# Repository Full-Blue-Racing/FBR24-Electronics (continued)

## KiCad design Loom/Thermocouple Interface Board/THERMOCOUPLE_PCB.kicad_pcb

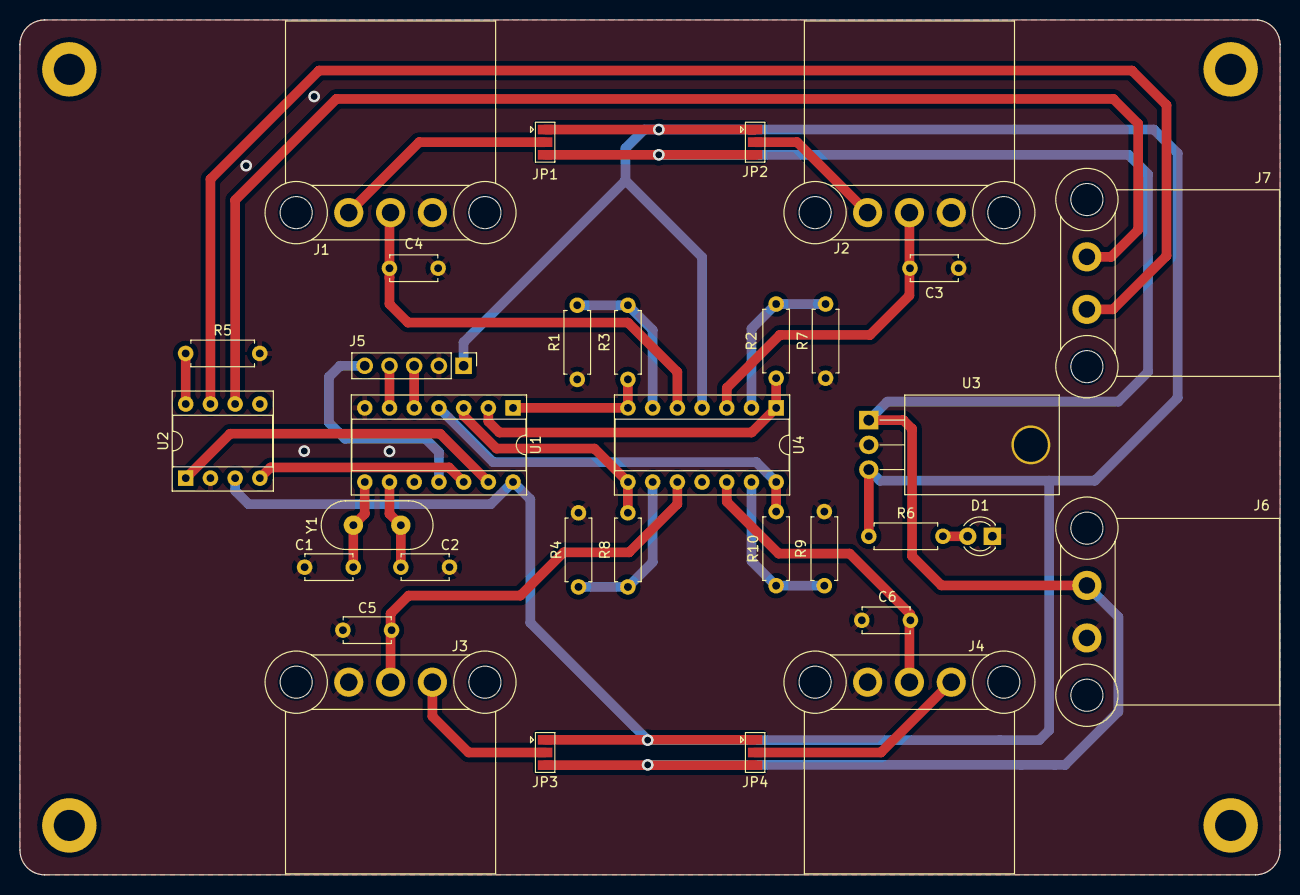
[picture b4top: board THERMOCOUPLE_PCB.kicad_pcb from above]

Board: 2 copper layers, 129.5 x 87.9 mm, 33 parts (0 on the bottom side), 30 nets.

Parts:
C1, C2: 27pF; C_Disc_D4.7mm_W2.5mm_P5.00mm
C3, C4, C5, C6: TBD; C_Disc_D4.7mm_W2.5mm_P5.00mm
D1: PWR LED; LED_D3.0mm
J1, J2, J3, J4: Conn_01x03; ATF13-3P-BM03
J5: Conn_01x05_Pin; PinHeader_1x05_P2.54mm_Vertical
J6, J7: Conn_01x02; ATF13-2P-BM03
JP1, JP2, JP3, JP4: SolderJumper_3_Open; SolderJumper-3_P1.3mm_Open_Pad1.0x1.5mm
R1, R2, R3, R4, R6, R7, R8, R9, R10: 220R; R_Axial_DIN0207_L6.3mm_D2.5mm_P7.62mm_Horizontal
R5: 20K; R_Axial_DIN0207_L6.3mm_D2.5mm_P7.62mm_Horizontal
U1: DIP-14_W7.62mm_Socket
U2: MCP2551-I-P; DIP-8_W7.62mm_Socket
U3: TL780-05KCS; TO-220-3_Horizontal_TabDown
U4: MCP6004; DIP-14_W7.62mm_Socket
Y1: Crystal; 9B-16.000MAAJ-B

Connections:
+5V: J5.1, JP1.1 (A), JP2.1 (A), JP3.1 (A), JP4.1 (A), R6.1, U1.14 (VDD), U2.3 (VDD), U3.3 (VO), U4.4 (V+)
+12V: J6.2, JP1.3 (B), JP2.3 (B), JP3.3 (B), JP4.3 (B), U3.1 (VI)
/AN0: R3.2, U1.1 (GP0), U4.7
/AN1: R2.2, U1.2 (GP1), U4.1
/AN2: R8.2, U1.3 (GP2), U4.8
/AN3: R10.2, U1.4 (GP3), U4.14
/CLK: J5.4, U1.6 (GP5)
/DATA: J5.3, U1.5 (GP4)
/PWR LED: D1.2 (A), R6.2
/RXCAN: U1.12 (RXCAN), U2.4 (RXD)
/TXCAN: U1.13 (TXCAN), U2.1 (TXD)
/VPP: J5.5, U1.11 (GP7)
GND: C1.2, C2.2, C3.2, C4.2, C5.2, C6.2, D1.1 (K), J1.1, J2.1, J3.1, J4.1, J5.2, J6.1, R1.1, R4.1, R5.2, R7.1, R9.1, U1.7 (VSS), U2.2 (VSS), U3.2 (GND)
unnamed: C4.1, J1.2, U4.5 (+)
unnamed: J1.3, JP1.2 (C)
unnamed: C3.1, J2.2, U4.3 (+)
unnamed: J2.3, JP2.2 (C)
unnamed: C5.1, J3.2, U4.10 (+)
unnamed: J3.3, JP3.2 (C)
unnamed: C6.1, J4.2, U4.12 (+)
unnamed: J4.3, JP4.2 (C)
unnamed: J7.1, U2.7 (CANH)
unnamed: J7.2, U2.6 (CANL)
unnamed: C1.1, U1.8 (OSC1), Y1.1
unnamed: C2.1, U1.9 (OSC2), Y1.2
unnamed: R5.1, U2.8 (Rs)
unnamed: R2.1, R7.2, U4.2 (-)
unnamed: R1.2, R3.1, U4.6 (-)
unnamed: R4.2, R8.1, U4.9 (-)
unnamed: R9.2, R10.1, U4.13 (-)

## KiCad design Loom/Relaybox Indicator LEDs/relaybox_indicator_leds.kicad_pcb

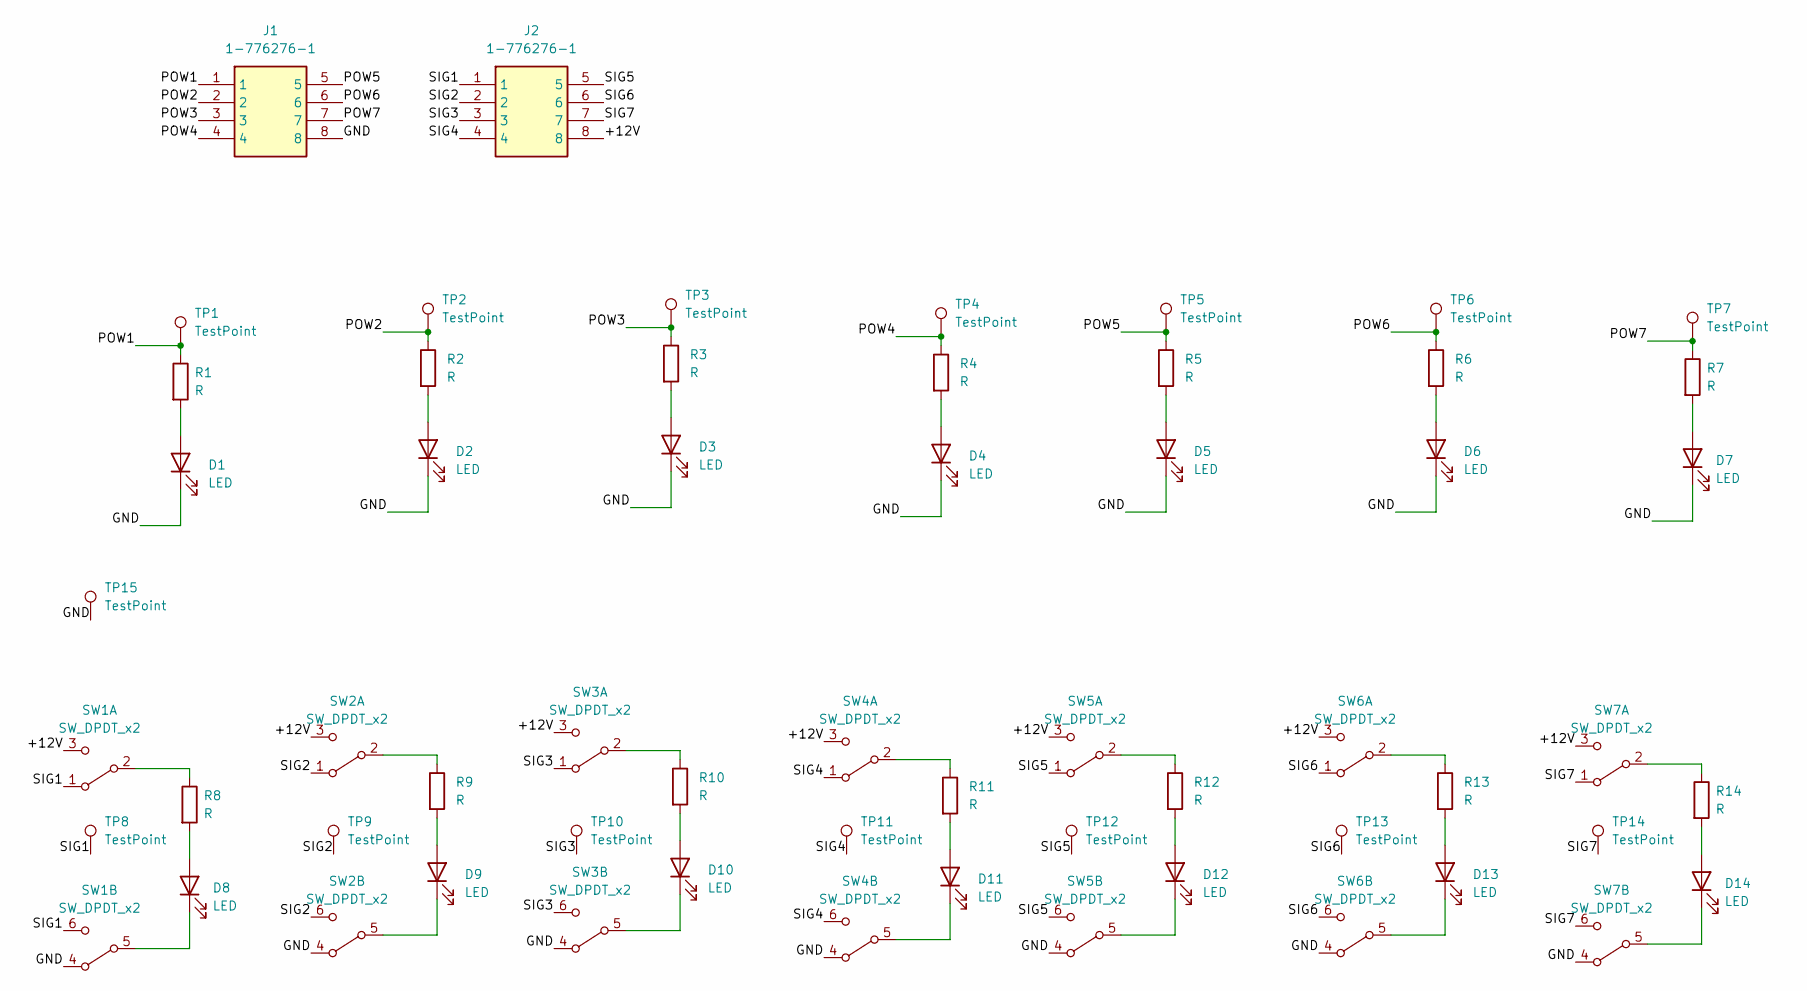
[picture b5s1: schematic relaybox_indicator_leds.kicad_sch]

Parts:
D1, D2, D3, D4, D5, D6, D7, D8, D9, D10, D11, D12, D13, D14: LED; LED_D5.0mm
J1, J2: 1-776276-1; 17762761; Mouser Part Number 571-1-776276-1
R1, R2, R3, R4, R5, R6, R7, R8, R9, R10, R11, R12, R13, R14: R; R_Axial_DIN0207_L6.3mm_D2.5mm_P10.16mm_Horizontal
SW1, SW2, SW3, SW4, SW5, SW6, SW7: SW_DPDT_x2; MP004696
TP1, TP2, TP3, TP4, TP5, TP6, TP7, TP8, TP9, TP10, TP11, TP12, TP13, TP14, TP15: TestPoint; TestPoint_THTPad_D3.0mm_Drill1.5mm

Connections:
/+12V: J2.8, SW1.3 (C), SW2.3 (C), SW3.3 (C), SW4.3 (C), SW5.3 (C), SW6.3 (C), SW7.3 (C)
/GND: D1.1 (K), D2.1 (K), D3.1 (K), D4.1 (K), D5.1 (K), D6.1 (K), D7.1 (K), J1.8, SW1.4 (A), SW2.4 (A), SW3.4 (A), SW4.4 (A), SW5.4 (A), SW6.4 (A), SW7.4 (A), TP15.1
/POW1: J1.1, R1.1, TP1.1
/POW2: J1.2, R2.1, TP2.1
/POW3: J1.3, R3.1, TP3.1
/POW4: J1.4, R4.1, TP4.1
/POW5: J1.5, R5.1, TP5.1
/POW6: J1.6, R6.1, TP6.1
/POW7: J1.7, R7.1, TP7.1
/SIG1: J2.1, SW1.1 (A), SW1.6 (C), TP8.1
/SIG2: J2.2, SW2.1 (A), SW2.6 (C), TP9.1
/SIG3: J2.3, SW3.1 (A), SW3.6 (C), TP10.1
/SIG4: J2.4, SW4.1 (A), SW4.6 (C), TP11.1
/SIG5: J2.5, SW5.1 (A), SW5.6 (C), TP12.1
/SIG6: J2.6, SW6.1 (A), SW6.6 (C), TP13.1
/SIG7: J2.7, SW7.1 (A), SW7.6 (C), TP14.1
unnamed: D1.2 (A), R1.2
unnamed: D2.2 (A), R2.2
unnamed: D3.2 (A), R3.2
unnamed: D4.2 (A), R4.2
unnamed: D5.2 (A), R5.2
unnamed: D6.2 (A), R6.2
unnamed: D7.2 (A), R7.2
unnamed: D8.2 (A), R8.2
unnamed: D8.1 (K), SW1.5 (B)
unnamed: D9.2 (A), R9.2
unnamed: D9.1 (K), SW2.5 (B)
unnamed: D10.2 (A), R10.2
unnamed: D10.1 (K), SW3.5 (B)
unnamed: D11.2 (A), R11.2
unnamed: D11.1 (K), SW4.5 (B)
unnamed: D12.2 (A), R12.2
unnamed: D12.1 (K), SW5.5 (B)
unnamed: D13.2 (A), R13.2
unnamed: D13.1 (K), SW6.5 (B)
unnamed: D14.2 (A), R14.2
unnamed: D14.1 (K), SW7.5 (B)
unnamed: R8.1, SW1.2 (B)
unnamed: R9.1, SW2.2 (B)
unnamed: R10.1, SW3.2 (B)
unnamed: R11.1, SW4.2 (B)
unnamed: R12.1, SW5.2 (B)
unnamed: R13.1, SW6.2 (B)
unnamed: R14.1, SW7.2 (B)

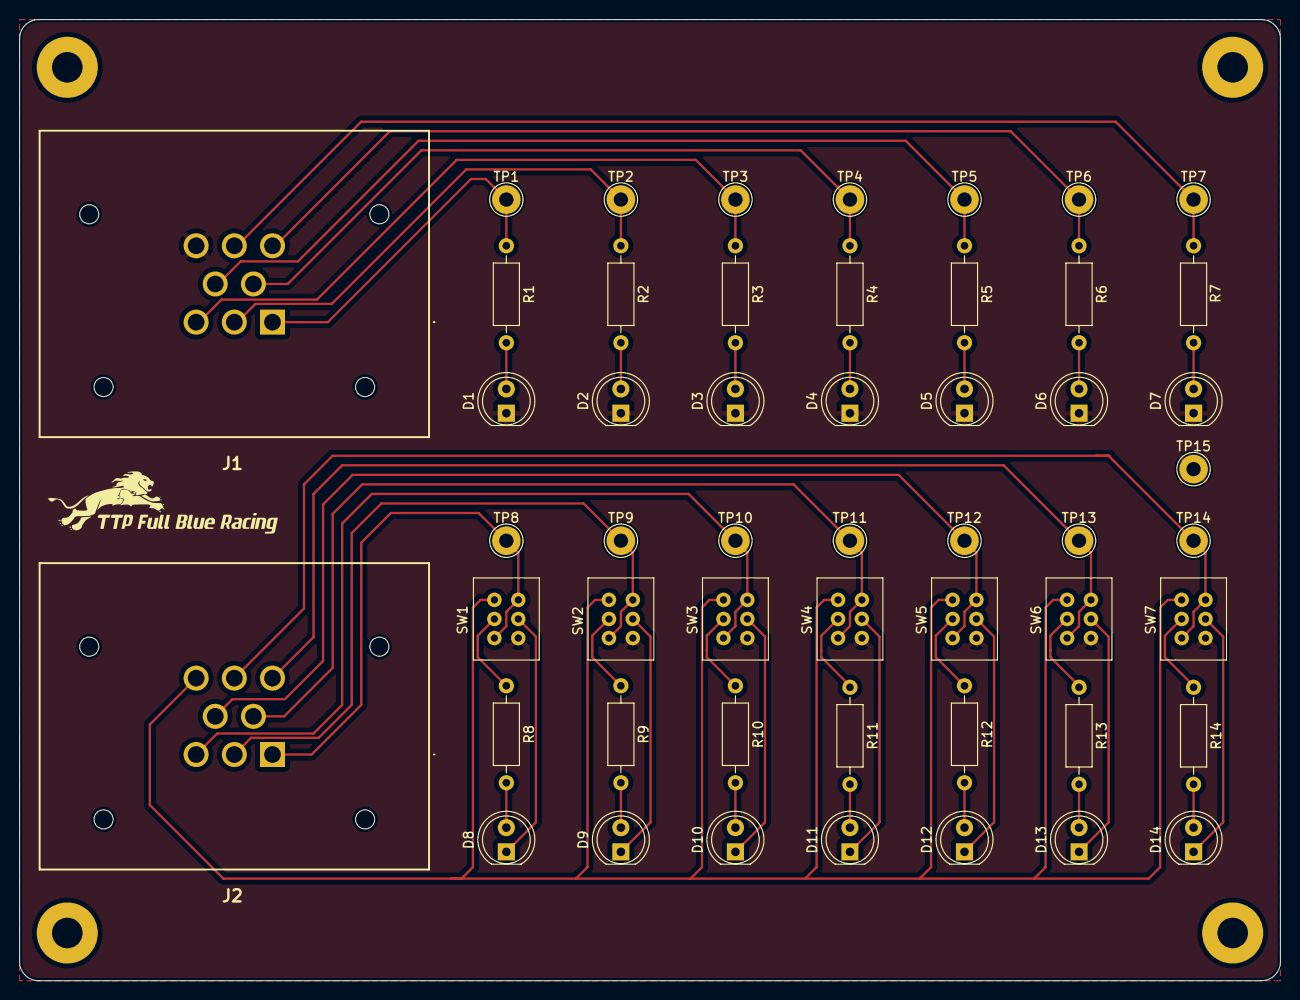
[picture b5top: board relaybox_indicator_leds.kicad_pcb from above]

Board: 2 copper layers, 132.1 x 100.7 mm, 52 parts (0 on the bottom side), 44 nets.

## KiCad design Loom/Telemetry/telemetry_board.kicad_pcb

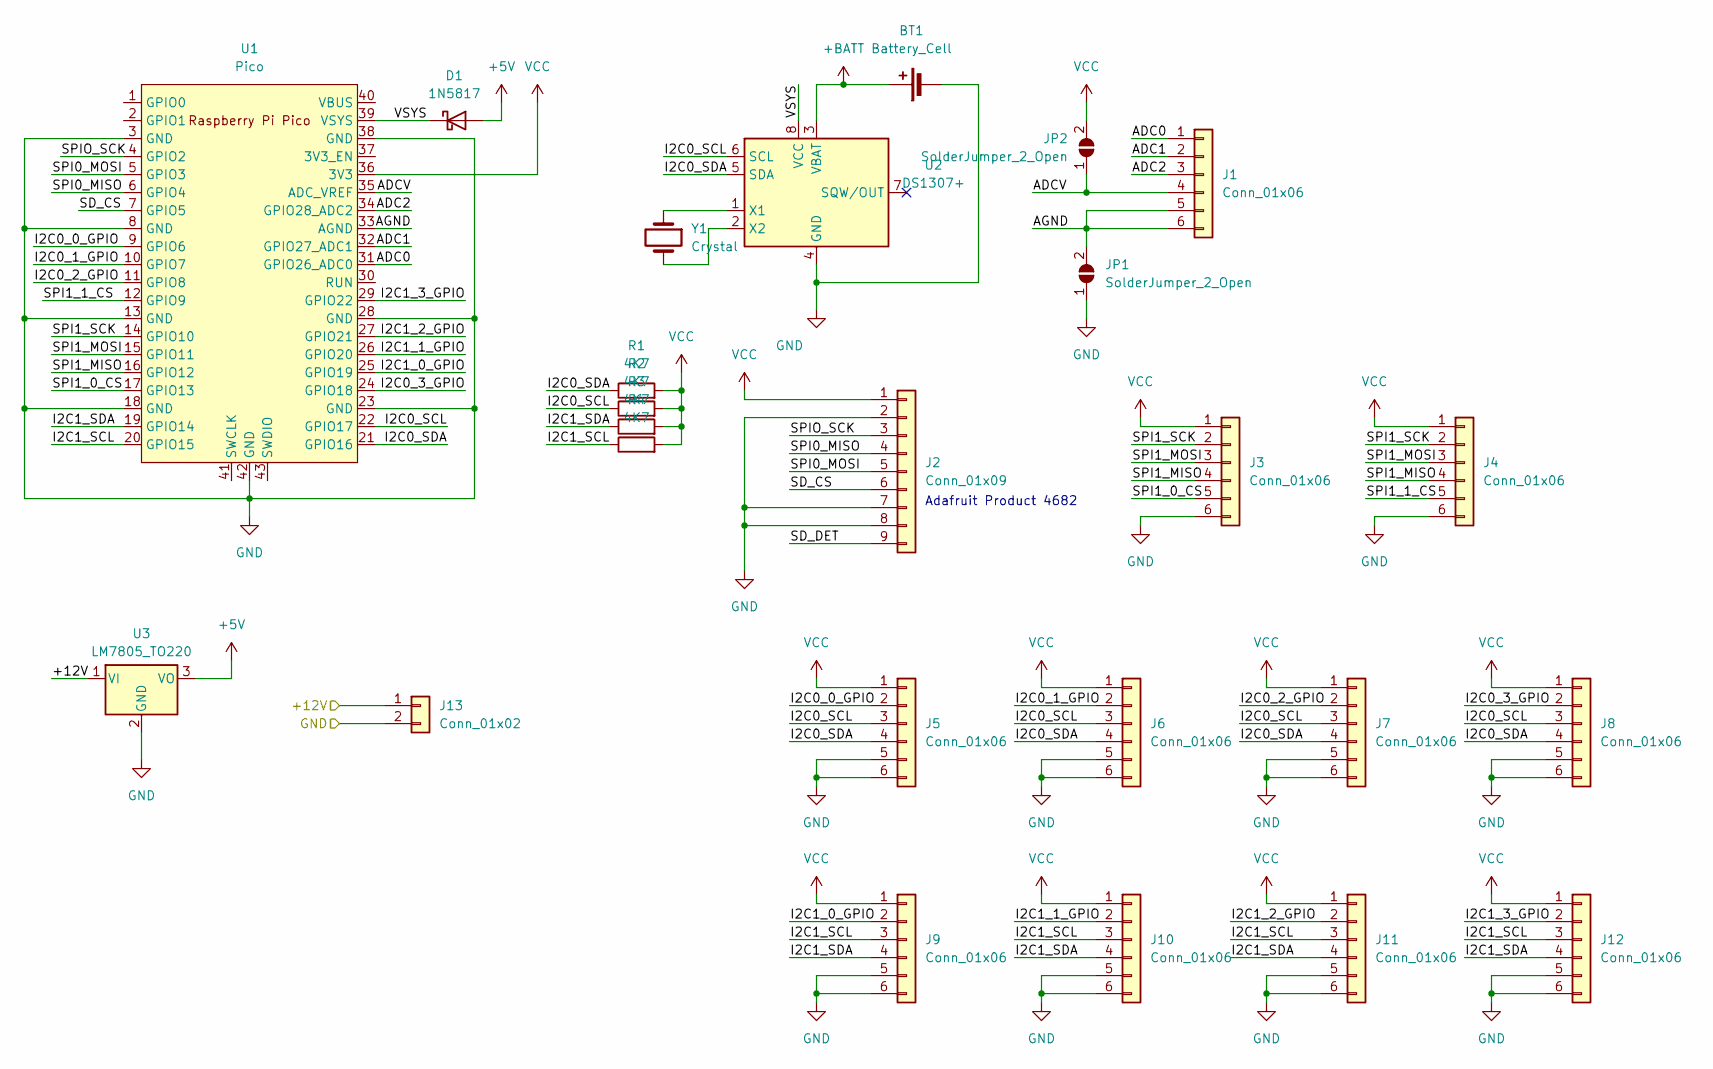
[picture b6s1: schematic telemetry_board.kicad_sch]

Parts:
BT1: Battery_Cell; RSPRO_237-8341
D1: 1N5817; D_DO-41_SOD81_P10.16mm_Horizontal
J1, J3, J4, J5, J6, J7, J8, J9, J10, J11, J12: Conn_01x06; JST_XA_B06B-XASK-1_1x06_P2.50mm_Vertical
J2: Conn_01x09; Adafruit_MicroSD_Breakout_4682
J13: Conn_01x02; TerminalBlock_bornier-2_P5.08mm
JP1, JP2: SolderJumper_2_Open; SolderJumper-2_P1.3mm_Open_Pad1.0x1.5mm
R1, R2, R3, R4: 4K7; R_Axial_DIN0207_L6.3mm_D2.5mm_P10.16mm_Horizontal
U1: Pico; RPi_Pico_W_SMD_TH
U2: DS1307+; DIP-8_W7.62mm
U3: LM7805_TO220; TO-220-3_Horizontal_TabDown
Y1: Crystal; Crystal_Round_D1.0mm_Vertical

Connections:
+5V: D1.2 (A), U3.3 (VO)
+12V: J13.1, U3.1 (VI)
+BATT: BT1.1 (+), U2.3 (VBAT)
ADC0: J1.1, U1.31 (GPIO26_ADC0)
ADC1: J1.2, U1.32 (GPIO27_ADC1)
ADC2: J1.3, U1.34 (GPIO28_ADC2)
ADCV: J1.4, JP2.1 (A), U1.35 (ADC_VREF)
AGND: J1.5, J1.6, JP1.2 (B), U1.33 (AGND)
GND: BT1.2 (-), J2.2, J2.7, J2.8, J3.6, J4.6, J5.5, J5.6, J6.5, J6.6, J7.5, J7.6, J8.5, J8.6, J9.5, J9.6, J10.5, J10.6, J11.5, J11.6, J12.5, J12.6, J13.2, JP1.1 (A), U1.3 (GND), U1.8 (GND), U1.13 (GND), U1.18 (GND), U1.23 (GND), U1.28 (GND), U1.38 (GND), U1.42 (GND), U2.4 (GND), U3.2 (GND)
I2C0_0_GPIO: J5.2, U1.9 (GPIO6)
I2C0_1_GPIO: J6.2, U1.10 (GPIO7)
I2C0_2_GPIO: J7.2, U1.11 (GPIO8)
I2C0_3_GPIO: J8.2, U1.24 (GPIO18)
I2C0_SCL: J5.3, J6.3, J7.3, J8.3, R2.1, U1.22 (GPIO17), U2.6 (SCL)
I2C0_SDA: J5.4, J6.4, J7.4, J8.4, R1.1, U1.21 (GPIO16), U2.5 (SDA)
I2C1_0_GPIO: J9.2, U1.25 (GPIO19)
I2C1_1_GPIO: J10.2, U1.26 (GPIO20)
I2C1_2_GPIO: J11.2, U1.27 (GPIO21)
I2C1_3_GPIO: J12.2, U1.29 (GPIO22)
I2C1_SCL: J9.3, J10.3, J11.3, J12.3, R4.1, U1.20 (GPIO15)
I2C1_SDA: J9.4, J10.4, J11.4, J12.4, R3.1, U1.19 (GPIO14)
unnamed: U2.1 (X1), Y1.1
unnamed: U2.2 (X2), Y1.2
SD_CS: J2.6, U1.7 (GPIO5)
SD_DET: J2.9
SPI0_MISO: J2.4, U1.6 (GPIO4)
SPI0_MOSI: J2.5, U1.5 (GPIO3)
SPI1_0_CS: J3.5, U1.17 (GPIO13)
SPI1_1_CS: J4.5, U1.12 (GPIO9)
SPI1_MISO: J3.4, J4.4, U1.16 (GPIO12)
SPI1_MOSI: J3.3, J4.3, U1.15 (GPIO11)
SPI1_SCK: J3.2, J4.2, U1.14 (GPIO10)
SPIO_SCK: J2.3, U1.4 (GPIO2)
VCC: J2.1, J3.1, J4.1, J5.1, J6.1, J7.1, J8.1, J9.1, J10.1, J11.1, J12.1, JP2.2 (B), R1.2, R2.2, R3.2, R4.2, U1.36 (3V3)
VSYS: D1.1 (K), U1.39 (VSYS), U2.8 (VCC)

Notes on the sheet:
Adafruit Product 4682

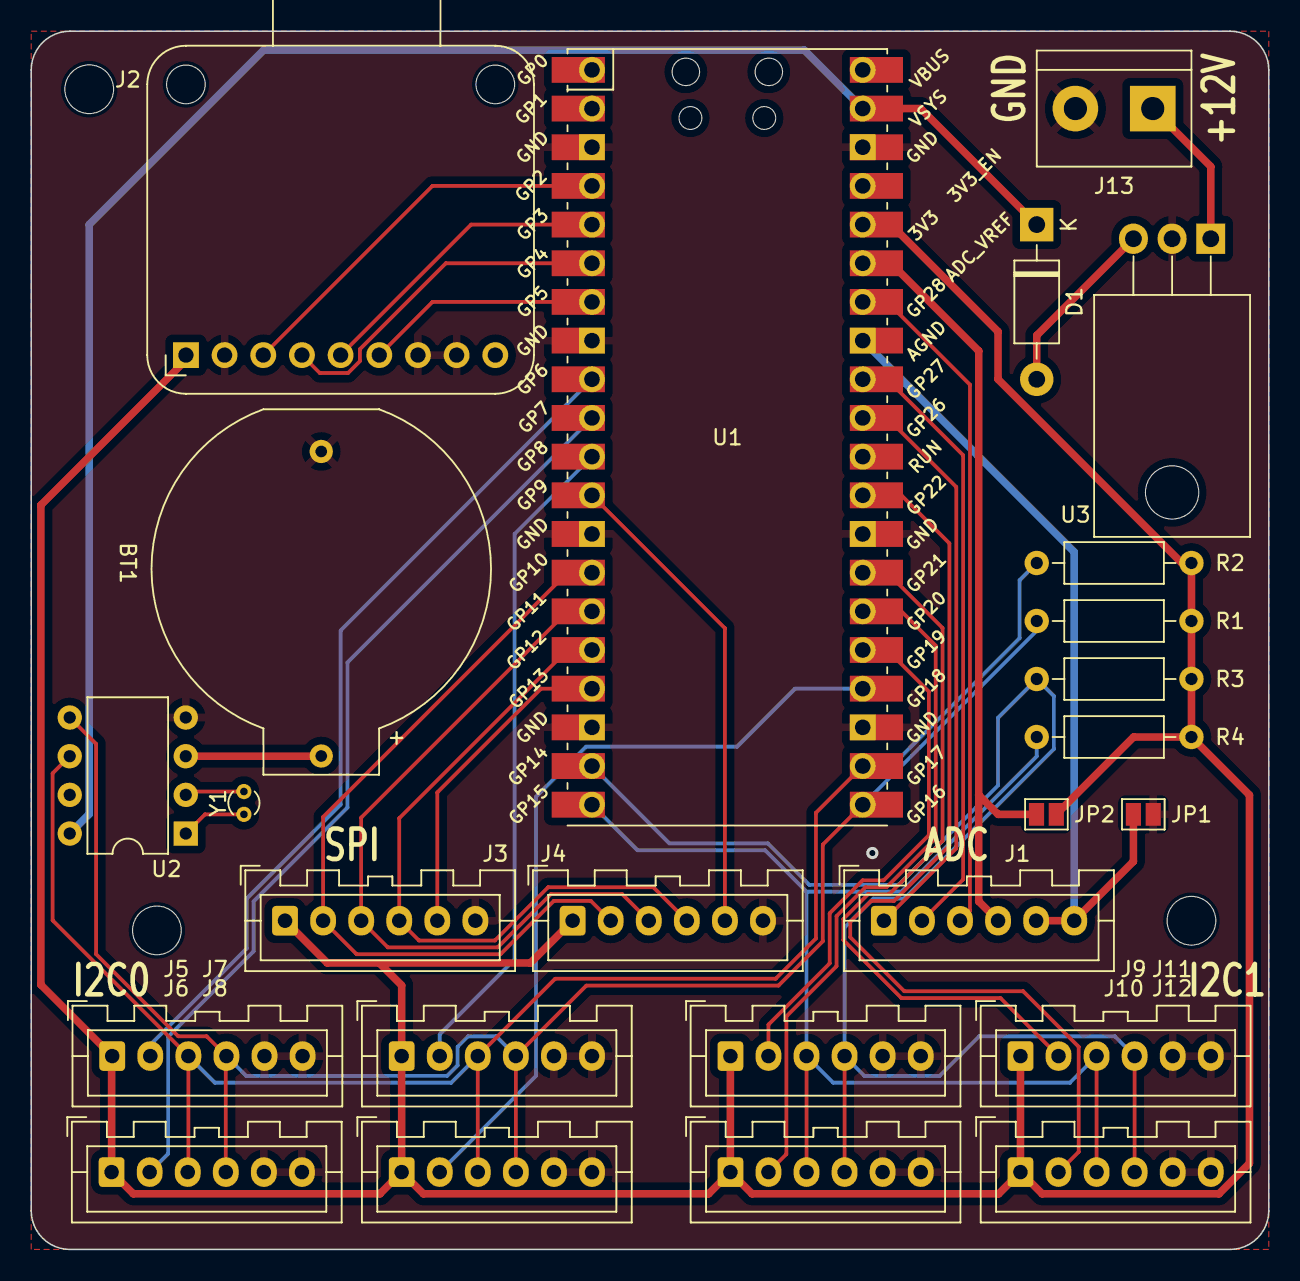
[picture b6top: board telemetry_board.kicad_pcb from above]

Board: 2 copper layers, 81.3 x 80.0 mm, 25 parts (0 on the bottom side), 34 nets.

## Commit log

2023-10-11 Added README
2023-10-15 Reorganized Loom folder
2023-10-15 Add start of new BSPD Design
    Currently just includes sensor inputs and the output, and not any
    of the actual logic.
2023-10-15 Add Labels to BPS/TPS Pins
2023-10-19 Complete most of BSPD State Machine
    TODO: Complete reset signal logic for state machine, to ensure
    we don't power in into a metastable or invalid state.
2023-10-22 Add KiCad caches to gitignore
2023-10-22 Add LogiSim Simulation of new BSPD
2023-10-22 Fix BSPD Timing
2023-10-22 added initial schemaic for can pcb
2023-10-22 Created relay LED schematic
2023-10-23 Add oscillator symbol
2023-10-23 Complete BSPD Schematic
2023-10-23 Schematic designed
2023-10-23 Added footprints and fixed component numbering
2023-10-24 PCB design
2023-10-29 Added the addional inputs to the schematic
2023-10-29 Removed islands and added rounded corners
2023-10-29 Complete Schematic, Footprint Assignment, Start PCB Design
2023-10-29 Add BOM
2023-10-30 CAN PCB initial layout and schematic changes
2023-10-30 Fix bug in state machine counters
    Realised that the reset counter would count even in an error
    condition, meaning that if 10 seconds pass after shutdown, it will
    turn back on instantly after the system is ok.
    Fixed by making the reset counter only count if system_ok is high
2023-10-30 Add State, Shutdown LEDs, Complete rough board layout
2023-10-31 Add .9in FBR Logo Footprint
2023-10-31 Complete New BSPD!
    TODO: Decide if the crystal needs a capacitor or not
2023-11-01 Complete Silkscreen, Fix DRC errors, Misc Cleanup
2023-11-03 Add filtering capacitor for crystal power
2023-11-04 Add mounting holes
2023-11-05 Update Loom Schematic with New BSPD
2023-11-12 Complete TelemetryCANBoard schematic
2023-11-12 Add test points
2023-11-12 Fix BSPD Test Points
2023-11-12 Add TelemetryCANBoard BOM
2023-11-12 Add NewBSPD BOM
2023-11-13 Made changes to can pcb layout
2023-11-13 Complete TelemetryCANBoard
2023-11-14 Fix CAN connector
2023-11-17 Minor layout and silkscreen changes
2023-11-19 Added thermocouple interface board files
2023-11-26 Generated gerbers
2023-11-27 minor changes
2023-11-27 Generated gerber files
2023-11-27 Revert "Merge branch 'CAN_PCB' of https://github.com/Full-Blue-Racing/FBR24-Electronics into CAN_PCB"
    This reverts commit f7426b5fd5c3026a458d075125f69338a8895489, reversing
    changes made to b85a40d8a8d15d08b24989522968470fc8db4cd4.
2023-11-27 Revert "Generated gerber files"
    This reverts commit b85a40d8a8d15d08b24989522968470fc8db4cd4.
2023-11-29 Add ATF13-2P to BSPD Footprints
2023-11-29 Change BSPD Power connector
2024-01-02 Minor changes to pass DRC
2024-01-28 Added various files
2024-05-12 Added relaybox indicators to main loom diagram
2024-05-12 Add gerbers
2024-05-15 Changes to the injector numbering
2024-05-18 Fixed injector high side labels
2024-05-19 Added the neutral and shutdown LEDs to dash
2024-05-19 Fix BSPD Crystal Footprint
2024-05-19 Update BSPD Gerbers
2024-05-19 Update Footprint 3D Model paths
    Make ATF13 footprint 3d model paths relative to ${KIPRJMOD} so they work on any machine.
